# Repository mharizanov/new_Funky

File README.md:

Funky v2
=========

The Funky v2 is a miniature Arduino Leonardo clone with RFM12B module, intended for low power, battery operated remote node. Due to the miniature size, only few carefully selected pins are available as a side header, none the less that is more than sufficient to interface several sensors at a time.

Having gained experience with my Funky v1 project, I decided to create a new version. The project is a success, yet the areas I wanted to optimize are

The Attiny84 MCU that was used in the Funky v1 has limited RAM and sketch memory
The Attiny84 requires an ISP programmer for sketch uploading
The Attiny84 required a modified Arduino core
Many of the available Arduino libraries are not compatible with Attiny84
So the Funky v2 was created, see my posts here , here and here

Board size is mere 22×22.8mm (0.87″x0.89″) in size (same as Funky v1)
The MCU used in an Atmega32U4, the same MCU that Arduino Leonardo uses. This makes the Funky v2 a minuature Arduino Leonardo compatible board with RFM12b module
The Funky v2 has the Caterina bootloader, so programming is done with Arduino IDE via micro USB
Uses external 8Mhz crystal (can switch to internal RC clock in software as described here)
Operates on 3.3V

Read more http://harizanov.com/wiki/wiki-home/funky-sensor-v2/

Licensed under a Creative Commons Attribution-NonCommercial-ShareAlike 3.0 Unported License.

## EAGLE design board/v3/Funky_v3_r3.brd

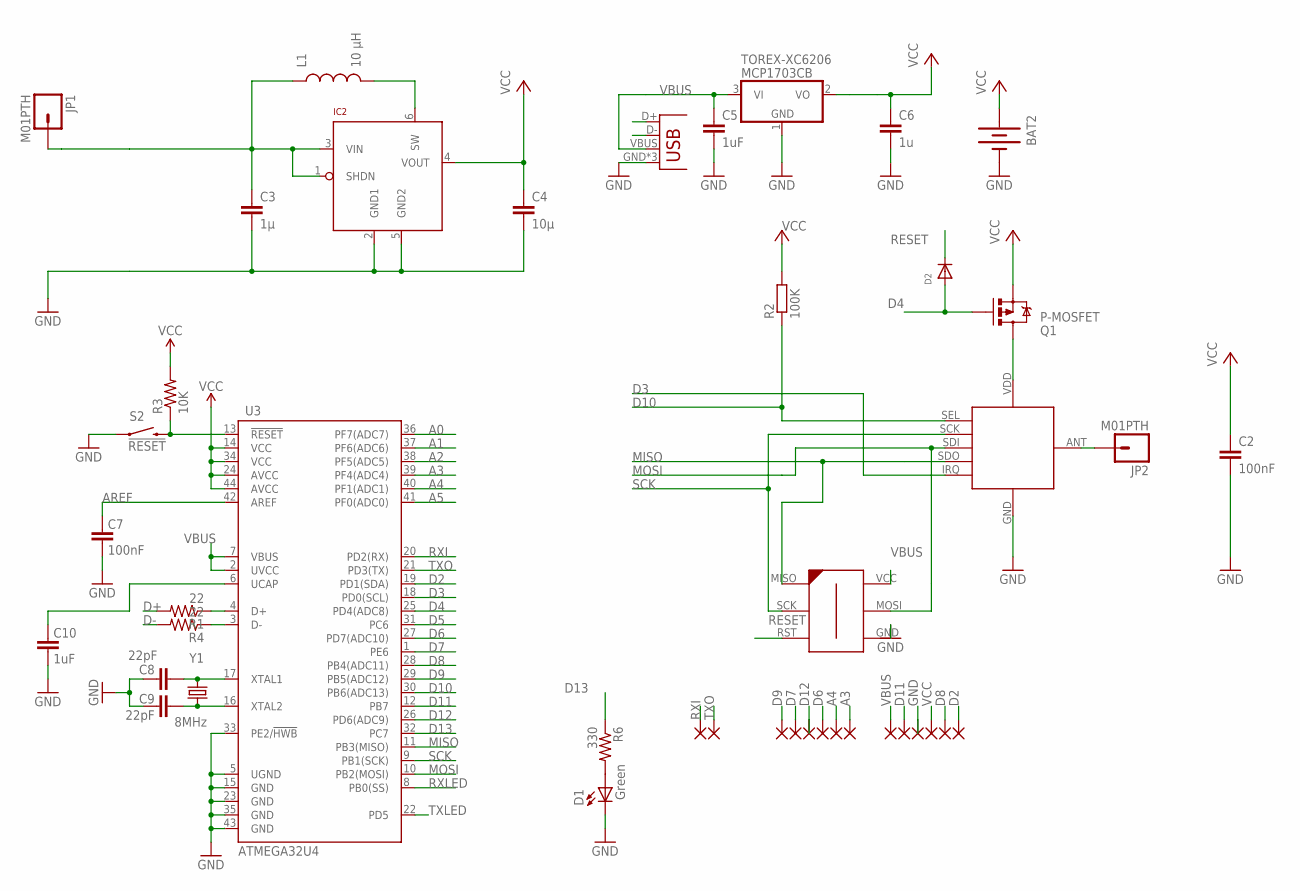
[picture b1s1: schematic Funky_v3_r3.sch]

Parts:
BAT2: BATTERY20PTH; BATTCOM_20MM_PTH
C2: 100nF; C0603K
C3: 1µ; 0603-CAP
C4: 10µ; 0805
C5: 1uF; C0603K
C6: 1u; C0603K
C7: 100nF; 0402-CAP
C8, C9: 22pF; 0402-CAP
C10: 1uF; 0402-CAP
D1: Green; LED-0603
D2: DIODESOD-323F; SOD-323F
IC2: LTC3525; SC70
JP1, JP2: M01PTH; 1X01
JP3: USB-MICROB
L1: 10 µH; 1210
PAD1, PAD2, PAD3, PAD4, PAD5, PAD6, PAD7, PAD8, PAD9, PAD10, PAD11, PAD12, PAD13, PAD14: SMD2; SMD1,27-2,54
Q1: P-MOSFET; SOT23
R1, R4: 22; 0402-RES
R2: 100K; R0402
R3: 10K; 0402-RES
R6: 330; 0402-RES
RFM12B1: RFM12B_MINPADS; RFM12B-MINPADS
S2: !RESET; TACTILE_SWITCH_SMD
TOREX-XC6206: MCP1703CB; SOT23
U3: ATMEGA32U4; QFN-44-NOPAD
U$2: AVR-ISP-6-EDGE; 6PAD_ISP
Y1: 8MHz; CRYSTAL-SMD-5X3

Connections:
A0: U3.36 (PF7(ADC7))
A1: U3.37 (PF6(ADC6))
A2: U3.38 (PF5(ADC5))
A3: PAD6.1, U3.39 (PF4(ADC4))
A4: PAD5.1, U3.40 (PF1(ADC1))
A5: U3.41 (PF0(ADC0))
AREF: C7.2, U3.42 (AREF)
D2: PAD12.1, U3.19 (PD1(SDA))
D3: RFM12B1.IRQ, U3.18 (PD0(SCL))
D4: D2.A, Q1.1 (G), U3.25 (PD4(ADC8))
D5: U3.31 (PC6)
D6: PAD4.1, U3.27 (PD7(ADC10))
D7: PAD2.1, U3.1 (PE6)
D8: PAD11.1, U3.28 (PB4(ADC11))
D9: PAD1.1, U3.29 (PB5(ADC12))
D10: R2.1, RFM12B1.SEL, U3.30 (PB6(ADC13))
D11: PAD7.1, U3.12 (PB7)
D12: PAD3.1, U3.26 (PD6(ADC9))
D13: R6.1, U3.32 (PC7)
D+: JP3.D+, R1.2
D-: JP3.D-, R4.2
GND: BAT2.2 (-), C2.2, C3.2, C4.2, C5.2, C6.2, C7.1, C8.2, C9.2, C10.1, D1.C, IC2.2 (GND1), IC2.5 (GND2), JP3.GND, JP3.MT1 (GND), JP3.MT2 (GND), PAD9.1, RFM12B1.GND, S2.1, TOREX-XC6206.1 (GND), U3.5 (UGND), U3.15 (GND), U3.23 (GND), U3.33 (PE2/!HWB), U3.35 (GND), U3.43 (GND), U$2.GND
MISO: RFM12B1.SDO (SDO/MISO), U3.11 (PB3(MISO)), U$2.MISO
MOSI: RFM12B1.SDI (SDI/MOSI), U3.10 (PB2(MOSI)), U$2.MOSI
unnamed: C9.1, U3.16 (XTAL2), Y1.1
unnamed: R1.1, U3.4 (D+)
unnamed: JP2.1, RFM12B1.ANT
unnamed: C8.1, U3.17 (XTAL1), Y1.3 (2)
unnamed: C10.2, U3.6 (UCAP)
unnamed: D1.A, R6.2
unnamed: R4.1, U3.3 (D-)
unnamed: Q1.3 (D), RFM12B1.VDD
unnamed: IC2.6 (SW), L1.2
RESET: D2.C, R3.1, S2.3 (2), U3.13 (!RESET), U$2.RST
RXI: PAD14.1, U3.20 (PD2(RX))
RXLED: U3.8 (PB0(SS))
SCK: RFM12B1.SCK, U3.9 (PB1(SCK)), U$2.SCK
TXLED: U3.22 (PD5)
TXO: PAD13.1, U3.21 (PD3(TX))
VBUS: C5.1, JP3.VBUS, PAD8.1, TOREX-XC6206.3 (VI), U3.2 (UVCC), U3.7 (VBUS), U$2.VCC
VCC: BAT2.1 (+), C2.1, C4.1, C6.1, IC2.4 (VOUT), PAD10.1, Q1.2 (S), R2.2, R3.2, TOREX-XC6206.2 (VO), U3.14 (VCC), U3.24 (AVCC), U3.34 (VCC), U3.44 (AVCC)
VIN: C3.1, IC2.1 (SHDN), IC2.3 (VIN), JP1.1, L1.1

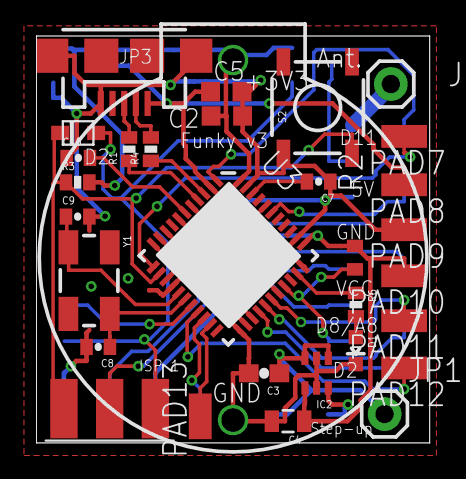
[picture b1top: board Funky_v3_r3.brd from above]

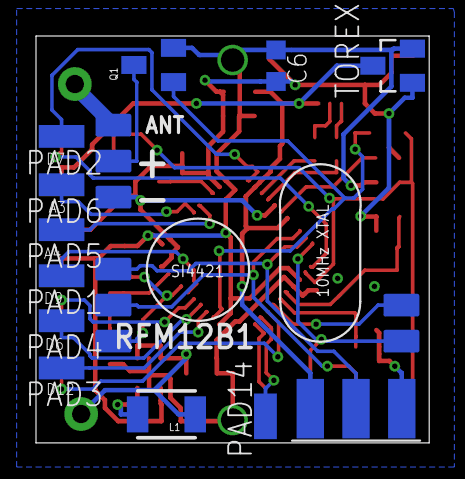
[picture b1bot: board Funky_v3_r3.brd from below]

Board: 2 copper layers, 21.8 x 22.6 mm, 43 parts (12 on the bottom side), 35 nets.

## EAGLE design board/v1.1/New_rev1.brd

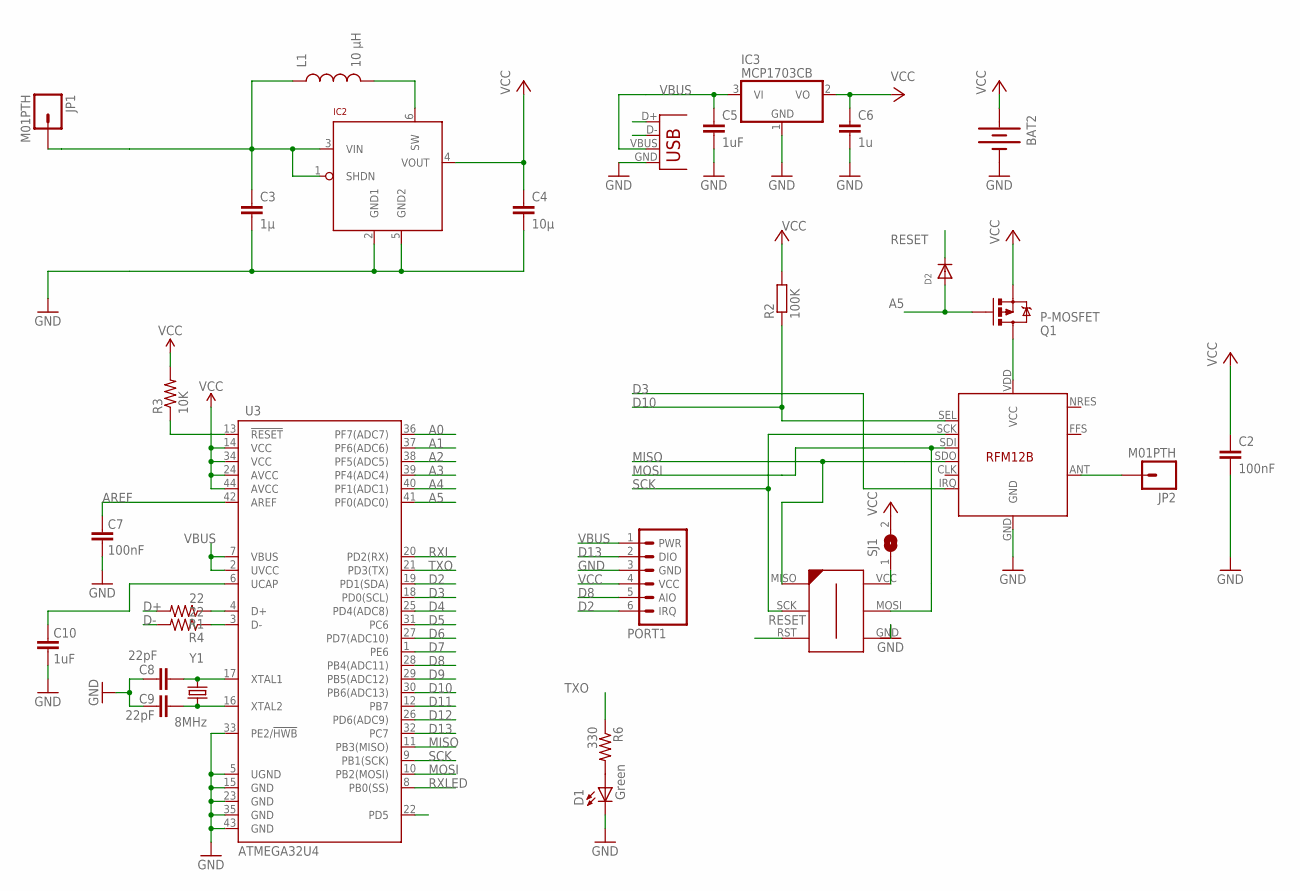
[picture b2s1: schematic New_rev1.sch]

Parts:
BAT2: BATTERY20PTH; BATTCOM_20MM_PTH
C2: 100nF; C0603K
C3: 1µ; 0603-CAP
C4: 10µ; 0805
C5: 1uF; C0603K
C6: 1u; C0603K
C7: 100nF; 0402-CAP
C8, C9: 22pF; 0402-CAP
C10: 1uF; 0402-CAP
D1: Green; LED-0603
D2: DIODESOD-323F; SOD-323F
IC2: LTC3525; SC70
IC3: MCP1703CB; SOT23
JP1, JP2: M01PTH; 1X01
L1: 10 µH; 1210
PORT1: JEEPORT-FEMALE; 1X06_FEMALE_LOCK.010
Q1: P-MOSFET; SOT23
R1, R4: 22; 0402-RES
R2: 100K; R0402
R3: 10K; 0402-RES
R6: 330; 0402-RES
RFM12B: RFM12B
SJ1: SJ
U3: ATMEGA32U4; QFN-44-NOPAD
U$2: AVR-ISP-6-EDGE; 6PAD_ISP
X1: USB-MICROB
Y1: 8MHz; CRYSTAL-SMD-5X3

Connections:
A0: U3.36 (PF7(ADC7))
A1: U3.37 (PF6(ADC6))
A2: U3.38 (PF5(ADC5))
A3: U3.39 (PF4(ADC4))
A4: U3.40 (PF1(ADC1))
A5: D2.A, Q1.1 (G), U3.41 (PF0(ADC0))
AREF: C7.2, U3.42 (AREF)
D2: PORT1.6 (IRQ), U3.19 (PD1(SDA))
D3: RFM12B.IRQ, U3.18 (PD0(SCL))
D4: U3.25 (PD4(ADC8))
D5: U3.31 (PC6)
D6: U3.27 (PD7(ADC10))
D7: U3.1 (PE6)
D8: PORT1.5 (AIO), U3.28 (PB4(ADC11))
D9: U3.29 (PB5(ADC12))
D10: R2.1, RFM12B.SEL, U3.30 (PB6(ADC13))
D11: U3.12 (PB7)
D12: U3.26 (PD6(ADC9))
D13: PORT1.2 (DIO), U3.32 (PC7)
D+: R1.2, X1.D+
D-: R4.2, X1.D-
GND: BAT2.2 (-), C2.2, C3.2, C4.2, C5.2, C6.2, C7.1, C8.2, C9.2, C10.1, D1.C, IC2.2 (GND1), IC2.5 (GND2), IC3.1 (GND), PORT1.3 (GND), RFM12B.GND, U3.5 (UGND), U3.15 (GND), U3.23 (GND), U3.33 (PE2/!HWB), U3.35 (GND), U3.43 (GND), U$2.GND, X1.GND
MISO: RFM12B.SDO, U3.11 (PB3(MISO)), U$2.MISO
MOSI: RFM12B.SDI, U3.10 (PB2(MOSI)), U$2.MOSI
unnamed: C9.1, U3.16 (XTAL2), Y1.1
unnamed: R1.1, U3.4 (D+)
unnamed: JP2.1, RFM12B.ANT
unnamed: C8.1, U3.17 (XTAL1), Y1.3 (2)
unnamed: C10.2, U3.6 (UCAP)
unnamed: D1.A, R6.2
unnamed: R4.1, U3.3 (D-)
unnamed: SJ1.1, U$2.VCC
unnamed: Q1.3 (D), RFM12B.VDD (VCC)
unnamed: IC2.6 (SW), L1.2
RESET: D2.C, R3.1, U3.13 (!RESET), U$2.RST
RXI: U3.20 (PD2(RX))
RXLED: U3.8 (PB0(SS))
SCK: RFM12B.SCK, U3.9 (PB1(SCK)), U$2.SCK
TXO: R6.1, U3.21 (PD3(TX))
VBUS: C5.1, IC3.3 (VI), PORT1.1 (PWR), U3.2 (UVCC), U3.7 (VBUS), X1.VBUS
VCC: BAT2.1 (+), C2.1, C4.1, C6.1, IC2.4 (VOUT), IC3.2 (VO), PORT1.4 (VCC), Q1.2 (S), R2.2, R3.2, SJ1.2, U3.14 (VCC), U3.24 (AVCC), U3.34 (VCC), U3.44 (AVCC)
VIN: C3.1, IC2.1 (SHDN), IC2.3 (VIN), JP1.1, L1.1

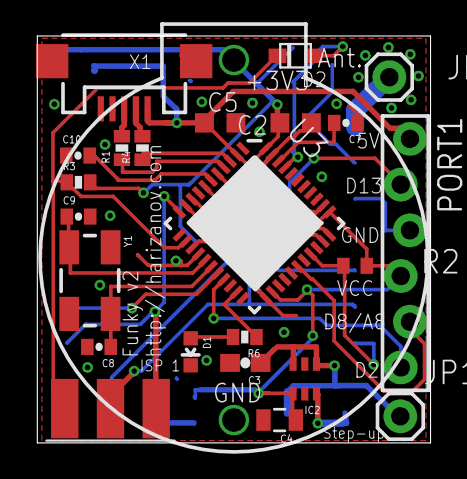
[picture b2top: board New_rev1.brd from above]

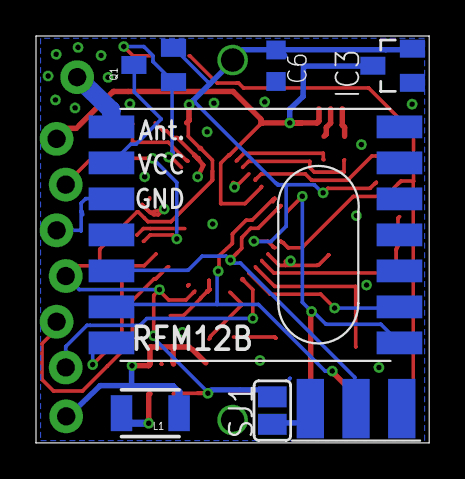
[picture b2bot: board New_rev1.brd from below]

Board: 2 copper layers, 21.8 x 22.6 mm, 30 parts (6 on the bottom side), 28 nets.

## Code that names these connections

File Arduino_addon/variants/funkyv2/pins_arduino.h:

/*
  pins_arduino.h - Pin definition functions for Arduino
  Part of Arduino - http://www.arduino.cc/

  Copyright (c) 2007 David A. Mellis

  This library is free software; you can redistribute it and/or
  modify it under the terms of the GNU Lesser General Public
  License as published by the Free Software Foundation; either
  version 2.1 of the License, or (at your option) any later version.

  This library is distributed in the hope that it will be useful,
  but WITHOUT ANY WARRANTY; without even the implied warranty of
  MERCHANTABILITY or FITNESS FOR A PARTICULAR PURPOSE.  See the GNU
  Lesser General Public License for more details.

  You should have received a copy of the GNU Lesser General
  Public License along with this library; if not, write to the
  Free Software Foundation, Inc., 59 Temple Place, Suite 330,
  Boston, MA  02111-1307  USA

  $Id: wiring.h 249 2007-02-03 16:52:51Z mellis $
*/

#ifndef Pins_Arduino_h
#define Pins_Arduino_h

#include <avr/pgmspace.h>

#define TX_RX_LED_INIT	DDRD |= (1<<5), DDRB |= (1<<0)
#define TXLED1			PORTD |= (1<<5)
#define TXLED0			PORTD &= ~(1<<5)
#define RXLED1			PORTB |= (1<<0)
#define RXLED0			PORTB &= ~(1<<0)

static const uint8_t SDA = 2;
static const uint8_t SCL = 3;

// Map SPI port to 'new' pins D14..D17
static const uint8_t SS   = 17;
static const uint8_t MOSI = 16;
static const uint8_t MISO = 14;
static const uint8_t SCK  = 15;

// Mapping of analog pins as digital I/O
// A6-A11 share with digital pins
static const uint8_t A0 = 18;
static const uint8_t A1 = 19;
static const uint8_t A2 = 20;
static const uint8_t A3 = 21;
static const uint8_t A4 = 22;
static const uint8_t A5 = 23;
static const uint8_t A6 = 24;	// D4
static const uint8_t A7 = 25;	// D6
static const uint8_t A8 = 26;	// D8
static const uint8_t A9 = 27;	// D9
static const uint8_t A10 = 28;	// D10
static const uint8_t A11 = 29;	// D12

#define digitalPinToPCICR(p)    ((((p) >= 8 && (p) <= 11) || ((p) >= 14 && (p) <= 17) || ((p) >= A8 && (p) <= A10)) ? (&PCICR) : ((uint8_t *)0))
#define digitalPinToPCICRbit(p) 0
#define digitalPinToPCMSK(p)    ((((p) >= 8 && (p) <= 11) || ((p) >= 14 && (p) <= 17) || ((p) >= A8 && (p) <= A10)) ? (&PCMSK0) : ((uint8_t *)0))
#define digitalPinToPCMSKbit(p) ( ((p) >= 8 && (p) <= 11) ? (p) - 4 : ((p) == 14 ? 3 : ((p) == 15 ? 1 : ((p) == 16 ? 2 : ((p) == 17 ? 0 : (p - A8 + 4))))))

//	__AVR_ATmega32U4__ has an unusual mapping of pins to channels
extern const uint8_t PROGMEM analog_pin_to_channel_PGM[];
#define analogPinToChannel(P)  ( pgm_read_byte( analog_pin_to_channel_PGM + (P) ) )

#ifdef ARDUINO_MAIN

// On the Arduino board, digital pins are also used
// for the analog output (software PWM).  Analog input
// pins are a separate set.

// ATMEL ATMEGA32U4 / ARDUINO LEONARDO
//
// D0				PD2					RXD1/INT2
// D1				PD3					TXD1/INT3
// D2				PD1		SDA			SDA/INT1
// D3#				PD0		PWM8/SCL	OC0B/SCL/INT0
// D4		A6		PD4					ADC8
// D5#				PC6		???			OC3A/#OC4A
// D6#		A7		PD7		FastPWM		#OC4D/ADC10
// D7				PE6					INT6/AIN0
//
// D8		A8		PB4					ADC11/PCINT4
// D9#		A9		PB5		PWM16		OC1A/#OC4B/ADC12/PCINT5
// D10#		A10		PB6		PWM16		OC1B/0c4B/ADC13/PCINT6
// D11#				PB7		PWM8/16		0C0A/OC1C/#RTS/PCINT7
// D12		A11		PD6					T1/#OC4D/ADC9
// D13#				PC7		PWM10		CLK0/OC4A
//
// A0		D18		PF7					ADC7
// A1		D19		PF6					ADC6
// A2		D20 	PF5					ADC5
// A3		D21 	PF4					ADC4
// A4		D22		PF1					ADC1
// A5		D23 	PF0					ADC0
//
// New pins D14..D17 to map SPI port to digital pins
//
// MISO		D14		PB3					MISO,PCINT3
// SCK		D15		PB1					SCK,PCINT1
// MOSI		D16		PB2					MOSI,PCINT2
// SS		D17		PB0					RXLED,SS/PCINT0
//
// TXLED			PD5
// RXLED		    PB0
// HWB				PE2					HWB

// these arrays map port names (e.g. port B) to the
// appropriate addresses for various functions (e.g. reading
// and writing)
const uint16_t PROGMEM port_to_mode_PGM[] = {
	NOT_A_PORT,
	NOT_A_PORT,
	(uint16_t) &DDRB,
	(uint16_t) &DDRC,
	(uint16_t) &DDRD,
	(uint16_t) &DDRE,
	(uint16_t) &DDRF,
};

const uint16_t PROGMEM port_to_output_PGM[] = {
	NOT_A_PORT,
	NOT_A_PORT,
	(uint16_t) &PORTB,
	(uint16_t) &PORTC,
	(uint16_t) &PORTD,
	(uint16_t) &PORTE,
	(uint16_t) &PORTF,
};

const uint16_t PROGMEM port_to_input_PGM[] = {
	NOT_A_PORT,
	NOT_A_PORT,
	(uint16_t) &PINB,
	(uint16_t) &PINC,
	(uint16_t) &PIND,
	(uint16_t) &PINE,
	(uint16_t) &PINF,
};

const uint8_t PROGMEM digital_pin_to_port_PGM[30] = {
	PD, // D0 - PD2
	PD,	// D1 - PD3
	PD, // D2 - PD1
	PD,	// D3 - PD0
	PD,	// D4 - PD4
	PC, // D5 - PC6
	PD, // D6 - PD7
	PE, // D7 - PE6
	
	PB, // D8 - PB4
	PB,	// D9 - PB5
	PB, // D10 - PB6
	PB,	// D11 - PB7
	PD, // D12 - PD6
	PC, // D13 - PC7
	
	PB,	// D14 - MISO - PB3
	PB,	// D15 - SCK - PB1
	PB,	// D16 - MOSI - PB2
	PB,	// D17 - SS - PB0
	
	PF,	// D18 - A0 - PF7
	PF, // D19 - A1 - PF6
	PF, // D20 - A2 - PF5
	PF, // D21 - A3 - PF4
	PF, // D22 - A4 - PF1
	PF, // D23 - A5 - PF0
	
	PD, // D24 / D4 - A6 - PD4
	PD, // D25 / D6 - A7 - PD7
	PB, // D26 / D8 - A8 - PB4
	PB, // D27 / D9 - A9 - PB5
	PB, // D28 / D10 - A10 - PB6
	PD, // D29 / D12 - A11 - PD6
};

const uint8_t PROGMEM digital_pin_to_bit_mask_PGM[30] = {
	_BV(2), // D0 - PD2
	_BV(3),	// D1 - PD3
	_BV(1), // D2 - PD1
	_BV(0),	// D3 - PD0
	_BV(4),	// D4 - PD4
	_BV(6), // D5 - PC6
	_BV(7), // D6 - PD7
	_BV(6), // D7 - PE6
	
	_BV(4), // D8 - PB4
	_BV(5),	// D9 - PB5
	_BV(6), // D10 - PB6
	_BV(7),	// D11 - PB7
	_BV(6), // D12 - PD6
	_BV(7), // D13 - PC7
	
	_BV(3),	// D14 - MISO - PB3
	_BV(1),	// D15 - SCK - PB1
	_BV(2),	// D16 - MOSI - PB2
	_BV(0),	// D17 - SS - PB0
	
	_BV(7),	// D18 - A0 - PF7
	_BV(6), // D19 - A1 - PF6
	_BV(5), // D20 - A2 - PF5
	_BV(4), // D21 - A3 - PF4
	_BV(1), // D22 - A4 - PF1
	_BV(0), // D23 - A5 - PF0
	
	_BV(4), // D24 / D4 - A6 - PD4
	_BV(7), // D25 / D6 - A7 - PD7
	_BV(4), // D26 / D8 - A8 - PB4
	_BV(5), // D27 / D9 - A9 - PB5
	_BV(6), // D28 / D10 - A10 - PB6
	_BV(6), // D29 / D12 - A11 - PD6
};

const uint8_t PROGMEM digital_pin_to_timer_PGM[16] = {
	NOT_ON_TIMER,	
	NOT_ON_TIMER,
	NOT_ON_TIMER,
	TIMER0B,		/* 3 */
	NOT_ON_TIMER,
	TIMER3A,		/* 5 */
	TIMER4D,		/* 6 */
	NOT_ON_TIMER,	
	
	NOT_ON_TIMER,	
	TIMER1A,		/* 9 */
	TIMER1B,		/* 10 */
	TIMER0A,		/* 11 */
	
	NOT_ON_TIMER,	
	TIMER4A,		/* 13 */
	
	NOT_ON_TIMER,	
	NOT_ON_TIMER,
};

const uint8_t PROGMEM analog_pin_to_channel_PGM[12] = {
	7,	// A0				PF7					ADC7
	6,	// A1				PF6					ADC6	
	5,	// A2				PF5					ADC5	
	4,	// A3				PF4					ADC4
	1,	// A4				PF1					ADC1	
	0,	// A5				PF0					ADC0	
	8,	// A6		D4		PD4					ADC8
	10,	// A7		D6		PD7					ADC10
	11,	// A8		D8		PB4					ADC11
	12,	// A9		D9		PB5					ADC12
	13,	// A10		D10		PB6					ADC13
	9	// A11		D12		PD6					ADC9
};

#endif /* ARDUINO_MAIN */
#endif /* Pins_Arduino_h */

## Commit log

2012-12-31 Initial
2013-01-05 some clearance fix
2013-02-19 PCB revision after the MISO/MOSI pins were messed up
2013-02-19 Examples
2013-02-25 Bash script to run on Raspberry Pi
2013-02-25 Python example
2013-03-17 Examples added/edited
2013-03-17 example
2013-03-17 Revert "example"
    This reverts commit 1f9ad8d22b45befcb35b8a9bb4ed2c9c1b9cff3c.
2013-03-20 Adding modded Caterina bootloader
2013-03-24 some more examples..
2013-03-26 refinements
2013-03-26 Rev 1.1 of the board
    added MOSFET to control RFM12B's power state
2013-03-26 ..refinements again
2013-03-28 ATmega32U4 Timer 4 experiments
2013-03-28 Increased a bit delay time for USB detect for Rpi
2013-03-29 Fix for Funky v2
2013-03-31 adding TCP/IP over serial example
2013-04-01 soil moisture project first draft
2013-04-04 I2C example
2013-04-18 new examples
2013-05-02 more examples
2013-05-29 adding lilypadusb bootloader
2013-06-02 keypad example
2013-06-12 reduce BOD to 2.2V
2013-06-17 latest
2013-06-17 added libs
2013-06-18 Fixed pin number for latest PCB layout
2013-06-18 ds18b20 example
2013-06-18 pin fix
2013-06-18 updated for the latest pcb revision with mosfet
2013-06-20 fixes
2013-06-22 Fixed Timer 0 disable
2013-06-22 optimization for a shorted led blink to save power
2013-06-24 increased delay to detect usb
2013-06-29 OLED and pulse counting examples
2013-07-01 rev 2 pcb files
2013-07-03 RF12demo added (JCW)
2013-07-06 bugs fixed
2013-07-06 updated code for better power efficiency
2013-07-07 removed old v1 header
2013-07-14 temperature to RGB example
2013-07-18 added OLED analog clock
2013-07-19 Fixed LED pin number (used workerB's)
2013-07-19 messed up code with workerB pins :( now fixed
2013-07-20 read vcc twice fix
2013-07-21 Optimization in startup
2013-07-21 Bugfix
2013-07-29 flood sensor example
2013-07-29 RFM12b earlier start
2013-08-04 battery level measurement fix
2013-08-07 IR to serial
2013-08-11 detect AC example
2013-08-12 DHT22 example
2013-08-24 door sensor example
2013-08-28 Clap detector example
2013-09-28 solar smart controller
2014-01-15 Funky v3 revision 3
2014-09-17 new example
2014-09-17 another example
2015-01-27 Examples update
2015-01-29 Updated RF12 Demo for Funky v3
    Note the Jeelib modification that is required
2015-01-29 Update the project folder to latet
2015-01-29 Adding .PNGs of board and schematic
2015-02-17 misc
2015-02-17 Correcting a missed LED_PIN define
    Correcting a missed LED_PIN define
2015-02-18 Fixed RFM12B_test to work for v3
2015-02-22 DHT22 example fix for Funky v3
2015-03-05 RF69 compatibility flag
2015-03-05 minor version fix
2015-03-26 RFM test updates
2015-03-27 DHT22 to serial example
2015-03-31 Jeelib is now fixed, so removing this comment
2015-04-04 Funky v3+RFM69CW using LowPowerLab's library test

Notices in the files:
parts and their libraries:
SparkFun: Licensing: CC v3.0 Share-Alike You are welcome to use this library for commercial purposes.
